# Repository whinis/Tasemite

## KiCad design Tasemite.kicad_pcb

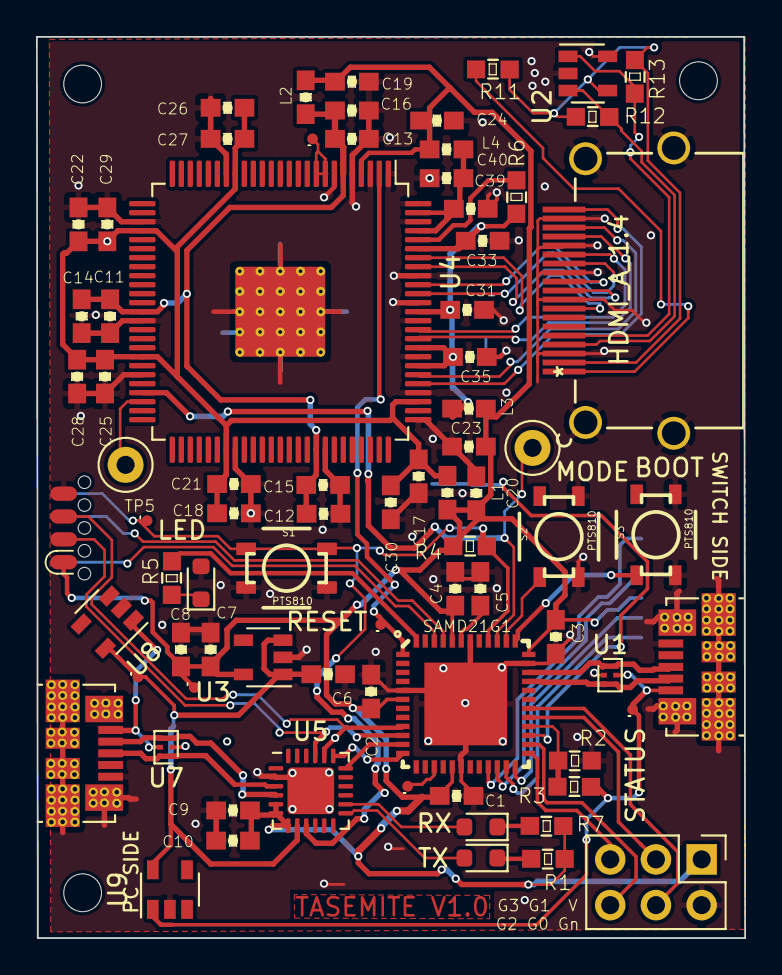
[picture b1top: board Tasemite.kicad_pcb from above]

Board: 2 copper layers, 39.3 x 50.1 mm, 82 parts (0 on the bottom side), 57 nets.

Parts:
C1, C2, C3, C4, C9: 100nf; C0603
C5, C6, C7, C10: 1uf; C0603
C8, C19, C20, C23, C24: 10uf; C0603
C11, C13, C15, C17, C21, C25, C27, C29, C31, C33, C35, C39: 100pf; C0603
C12, C14, C16, C18, C22, C26, C28, C30, C40: 2.2uf; C0603
H1, H2, H3: MountingHole; MountingHole_2.1mm
J1: Conn_02x04_Odd_Even; SOIC_clipProgSmall
J2, J3: USB_B_Micro; USB_Micro-B_Molex_47346-0001-Vias
J4: Conn_02x03_Odd_Even; PinHeader_2x03_P2.54mm_Vertical
J5: Micro_SD_Card_Det; MOLEX_503182-1852
J6: HDMI_A_1.4; 10029449-111RLF
L1, L2, L3, L4: INDUCTOR0603; C0603
R1, R5, R6, R7: 390; R0603
R2, R3, R4, R12, R13: 10k; R0603
R11: 2.7K; R0603
RX1, RX2: LEDCHIP-LED0603; LED_0603_1608Metric
S1, S2, S3: PTS810; TACTILE_SWITCH_SMD-4
SAMD21G1: ATSAMD21G17A-M; QFN48
TP1, TP2, TP4, TP6, TP8, TP13, TP19: TPTP06R; TP06R
TP3, TP5: TestPoint; TestPoint_Loop_D2.50mm_Drill1.0mm
TX1: LEDCHIP-LED0603; LED_0603_1608Metric
U1, U7: PRTR5V0U2F; SOT-886
U2: 24LC02BT; SOT-23-5
U3: MIC5504-3.3YM5; SOT-23-5
U4: SiI_163B-Sync; TQFP-100-1EP_14x14mm_P0.5mm_EP5x5mm_ThermalVias
U5: CP2102N-A01-GQFN24; QFN-24-1EP_4x4mm_P0.5mm_EP2.6x2.6mm
U8, U9: MAX40200AUK; SOT-23-5

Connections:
/3v3: C1.2, C2.2, C3.2, C4.2, C7.1, C8.2, C9.1, C10.1, C19.1, C20.1, C23.1, C24.1, J1.1, J4.1, J5.4, L1.2, L2.2, L3.2, L4.2, R1.1, R4.1, R7.1, SAMD21G1.6, SAMD21G1.17, SAMD21G1.36, SAMD21G1.44, TP19.TP, U3.5, U4.4, U5.5, U5.6, U5.7
/5v: J6.18, R11.2, R12.1, R13.1, U2.4
/BOOTLOADER: S3.A1, S3.A2, SAMD21G1.37
/CYCLE_TIME: SAMD21G1.15, TP2.TP
/GND: C1.1, C2.1, C3.1, C4.1, C5.1, C6.2, C7.2, C8.1, C9.2, C10.2, C11.2, C12.2, C13.2, C14.2, C15.2, C16.2, C17.2, C18.2, C19.2, C20.2, C21.2, C22.2, C23.2, C24.2, C25.2, C26.2, C27.2, C28.2, C29.2, C30.2, C31.2, C33.2, C35.2, C39.2, C40.2, J1.7, J2.5, J2.6, J3.5, J3.6, J4.2, J5.6, J5.10, J5.11, J6.2, J6.5, J6.8, J6.11, J6.17, J6.SH, R2.1, RX2.2, S1.B1, S1.B2, S2.B1, S2.B2, S3.B1, S3.B2, SAMD21G1.5, SAMD21G1.18, SAMD21G1.35, SAMD21G1.42, SAMD21G1.EP, U1.2, U2.2, U2.5, U3.2, U4.1, U4.3, U4.5, U4.7, U4.19, U4.28, U4.39, U4.45, U4.58, U4.68, U4.76, U4.79, U4.83, U4.87, U4.89, U4.92, U4.98, U4.100, U4.101, U5.2, U5.25, U7.2, U8.2, U9.2
/GPIO0: J4.4, SAMD21G1.30
/GPIO1: J4.3, SAMD21G1.29
/GPIO2: J4.6, SAMD21G1.26
/GPIO3: J4.5, SAMD21G1.25
/HDMI_PD: SAMD21G1.1, TP4.TP, U4.2
/HPD: J6.19, R11.1
/HSYNC: TP5.1, U4.48
/MCUCTS: SAMD21G1.12, U5.19
/MCURTS: SAMD21G1.11, U5.18
/MCURX: J1.3, SAMD21G1.10, U5.21
/MCUTX: J1.5, SAMD21G1.9, U5.20
/MCU_LED: R5.2, SAMD21G1.48
/MODE: S2.A1, S2.A2, SAMD21G1.38
/P_VBUS: J3.1, U7.5, U8.1
/RST: J1.8, R4.2, S1.A1, S1.A2, SAMD21G1.40, TP8.TP, U5.9
/RX_LED: RX1.2, U5.13
/Rx0+: J6.7, U4.90
/Rx0-: J6.9, U4.91
/Rx1+: J6.4, U4.85
/Rx1-: J6.6, U4.86
/Rx2+: J6.1, U4.80
/Rx2-: J6.3, U4.81
/RxC+: J6.10, U4.93
/RxC-: J6.12, U4.94
/SCL: J6.15, R13.2, U2.1
/SDA: J6.16, R12.2, U2.3
/SD_CD: J5.9, SAMD21G1.27
/SD_CE: J5.2, SAMD21G1.23
/SD_CLK: J5.5, SAMD21G1.22
/SD_SI: J5.3, SAMD21G1.24
/SD_SO: J5.7, SAMD21G1.21
/SWCLK: J1.6, SAMD21G1.45
/SWDIO: J1.2, SAMD21G1.46
/SWITCH_DETECT: R2.2, R3.1, SAMD21G1.28
/S_VBUS: J2.1, R3.2, TP6.TP, U1.5, U9.1
/Sheet5EC9C89B/AVCC: C31.1, C33.1, C35.1, L3.1, R6.2, U4.82, U4.84, U4.88, U4.95
/Sheet5EC9C89B/HVCC: C11.1, C12.1, C13.1, C14.1, C15.1, C16.1, L2.1, U4.6, U4.38, U4.67
/Sheet5EC9C89B/OVCC: C17.1, C18.1, C21.1, C22.1, C25.1, C26.1, C27.1, C28.1, C29.1, C30.1, L1.1, U4.18, U4.29, U4.43, U4.57, U4.78
/Sheet5EC9C89B/PVCC: C39.1, C40.1, L4.1, U4.97, U4.99
/TX_LED: TX1.2, U5.14
/USB2_N: J3.2, U5.4, U7.3, U7.4
/USB2_P: J3.3, U5.3, U7.1, U7.6
/USB_N: J2.2, SAMD21G1.33, U1.3, U1.4
/USB_P: J2.3, SAMD21G1.34, U1.1, U1.6
/VBUS: C6.1, TP13.TP, U3.1, U3.3, U5.8, U8.5, U9.5
/VDDCORE: C5.2, SAMD21G1.43
/VSYNC: SAMD21G1.39, TP3.1, U4.47
unnamed: R1.2, RX1.1
unnamed: R5.1, RX2.1
unnamed: R6.1, U4.96
unnamed: R7.2, TX1.1
unnamed: TP1.TP, U4.8, U4.9

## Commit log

2020-11-27 First commit of Tasemite including board and HDMI EEPROM programming

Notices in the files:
parts and their libraries:
Copyright 2016 Accelerated Designs. All rights reserved.
